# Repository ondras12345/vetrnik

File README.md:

# vetrnik
Power electronics for heating water using power generated by a small wind
turbine.

## Features / design goals
- No battery.
- Maximum power point tracking.
- Power to resistive heating elements is AC to prevent electrolytic corrosion.
- MQTT telemetry.
- Home Assistant integration via MQTT.
- Energy meter.
- Calculates RPM from wind turbine AC output frequency.
- Survives full 50 V / 40 A during normal operation, as well as significantly
  higher open-circuit voltage.

The device offers a feature-rich command line interface:
```
vetrnik-control:$ help
---- Available commands ----

SPIflash: Issue commands to SPI flash
conf: Get or set configuration options.
control: Get or set params of control algorithm.
debug: Filter debug messages
dfu: Switch to DFU firmware download mode.
ds18b20: Print out DS18B20 sensor readings
free: Print out amount of free memory.
ifconfig: Print out networking information.
lisp: Process a line of Lisp
lisp_read: Execute Lisp from file
lisp_reset: Reinit Lisp interpreter
log: Print log / postmort
millis: Returns the number of milliseconds passed since the program started.
mqtt: Print out MQTT status.
onewirescan: Scan devices on onewire bus
ota: Switch to over-the-air firmware dl mode.
power: Print status of power PCB or set params.
pump: Control circulation pump.
reset: Reset the MCU.
rx: Print out RX_datapoints.
rx_raw: Toggle printing of messages from power board.
stats: Get stats (energy, ...)
tx: Set value of TX datapoint.
tx_raw: Transmit message to power board.
uptime: Returns the time passed since the program started.
ver: Print out version info.
watch: Run command every second.

vetrnik-control:$ stats
stats:
energy: 0.000 kWh

vetrnik-control:$ power
power board status:
retrieved_millis: 2274816315
valid: 1
time: 56810 s
mode: 2
duty: 0 (0-255)
OCP_max_duty: 255 (0-255)
RPM: 0 RPM
voltage: 0.0 V
current: 0.000 A
enabled.hardware: 1
enabled.software: 1
enabled.overall: 1
emergency: 0
temperature_heatsink: 16.3 'C
temperature_rectifier: 16.4 'C
fan: 0
error_count: 0
last5m: 0

vetrnik-control:$ ds18b20
This command does NOT request a new conversion.
[0] voda: 28.93 C
[1] : 0.00 C
[2] : 0.00 C
[3] : 0.00 C
[4] : 0.00 C
[5] : 0.00 C
[6] : 0.00 C
[7] : 0.00 C
[8] : 0.00 C
[9] : 0.00 C

vetrnik-control:$ SPIflash -h
Usage: SPIflash [erase_chip|ls | create name length erasable | rm name
   | dump name start | dumpchip start | erase filename | ed filename start]

vetrnik-control:$ SPIflash ls
Files:
address (HEX)	name	size (Bytes)
010000	settings	65536
020000	init.lisp	65536

vetrnik-control:$ lisp (= test (/ (+ 1 3) 2))
nil
Success: 1

vetrnik-control:$ lisp test
2
Success: 1

vetrnik-control:$ log
Usage: log (all|new)

vetrnik-control:$ log all
Printing whole log...
---
[      0] event: 0x0D log reinit
[      0] boot: 0x05 POWER-ON_RESET (POR) / POWER-DOWN_RESET (PDR)
[      0] event: 0x00 Eth begin
[      5] event: 0x01 Eth got IP
[      5] control strategy: old=control_shorted new=control_shorted
[      5] MQTT state: -1 DISCONNECTED
[     20] event: 0x03 MQTT connected
[     21] MQTT state: 0 CONNECTED
[   6315] control strategy: old=control_shorted new=control_lisp
[  82610] event: 0x10 DS18B20 error
[ 966931] MQTT state: -3 CONNECTION_LOST
[ 966932] event: 0x03 MQTT connected
[ 966932] MQTT state: 0 CONNECTED
[3386627] MQTT state: -2 CONNECT_FAILED
[3386810] event: 0x03 MQTT connected
[3386810] MQTT state: 0 CONNECTED
[3386870] event: 0x03 MQTT connected
[3387652] MQTT state: -3 CONNECTION_LOST
[3387652] event: 0x03 MQTT connected
[3387652] MQTT state: 0 CONNECTED
[3387712] event: 0x03 MQTT connected
[3387772] MQTT state: -3 CONNECTION_LOST
[3387772] event: 0x03 MQTT connected
[3387772] MQTT state: 0 CONNECTED
[3387814] control strategy: old=control_lisp new=control_shorted
[      0] boot: 0x04 SOFTWARE_RESET
[      0] event: 0x00 Eth begin
[      5] event: 0x01 Eth got IP
[      5] control strategy: old=control_shorted new=control_shorted
[      5] MQTT state: -1 DISCONNECTED
[     20] event: 0x03 MQTT connected
[     20] MQTT state: 0 CONNECTED
[     28] MQTT receive: length=1
[     29] MQTT receive: length=11
[     29] control strategy: old=control_shorted new=control_lisp
[ 118759] MQTT state: -3 CONNECTION_LOST
[ 118760] event: 0x03 MQTT connected
[ 118760] MQTT state: 0 CONNECTED
[ 721373] MQTT state: -3 CONNECTION_LOST
[ 721373] MQTT state: -2 CONNECT_FAILED
[ 721414] event: 0x03 MQTT connected
[ 721414] MQTT state: 0 CONNECTED
[ 982793] MQTT state: -3 CONNECTION_LOST
[ 982794] event: 0x03 MQTT connected
[ 982794] MQTT state: 0 CONNECTED
[ 983379] MQTT state: -3 CONNECTION_LOST
[ 983380] event: 0x03 MQTT connected
[ 983380] MQTT state: 0 CONNECTED
[2274043] MQTT receive: length=1
[2274062] MQTT receive: length=1
done

vetrnik-control:$
```

## Hardware details
See [`hardware/`](hardware/).

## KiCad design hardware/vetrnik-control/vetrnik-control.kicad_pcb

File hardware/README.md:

# Vetrnik hardware
Block diagram:
```
            3 phase
+---------+ contactor +-----------+ DC +--------+ +-----------+ 1-phase +---------+
| Turbine +-+__/ __---+ rectifier +-+--+ ACS770 +-+ H-bridge  +---------+ heater  +
+---------+ |  ^      +-----------+ |  +----+---+ +-----------+ AC      +---------+
            |  |                    |       |          ^
            |  |             voltage|       |          |
            |  |                    |       | current  | duty
            |  |                    v       |          |
  frequency |  |      +-------------+-+     |          |
  (RPM)     |  +------+ vetrnik-power +<----+          |
            +-------->+               +----------------+
                      +-------+-------+
                              ^
                              | UART
                              v
                      +-------+-----------+
                      |  vetrnik-control  |
                      |                   +<----------> Ethernet
                      +-------------------+
```

The hardware consists of several PCBs in a custom-made enclosure. Most PCBs
are single-sided and designed to be milled out on a CNC.
- vetrnik-power
  - Controlled by an ATmega8 MCU.
  - Controls a FET H-bridge mounted on a heatsink.
  - Has isolated power supply, its GNDPWR is at wind turbine output potential.
  - Receives commands from vetrnik-control via optically isolated UART.
  - No remote firmware updates, no bootloader.
  - This PCB also contains analog comparator-based emergency stop circuitry
    that handles over-voltage condition even if the MCU is not working.
- vetrnik-control
  - Controlled by STM32F401.
  - Handles smart features (Ethernet, telnet, MQTT).
  - Implements LISP-like interpreted language that can be used to send
    commands to vetrnik-power. MPPT controller is implemented on this device
    in LISP.
  - Supports OTA firmware updates.
- vetrnik-current-sensor
  - A double-sided PCB with heavy copper. It passes all the current from the
    bridge rectifier through an ACS770-050U hall-effect current sensor.
- vetrnik-current-sensor-opamp
  - This PCB contains some additional signal-conditioning circuitry to improve
    current sensing precision and filter out noise.
- vetrnik-power-supply
  - A power supply board that converts 12 V from MeanWell power supply to
    various voltage levels needed by the device.
    The 3.3V voltage regulator is switch mode, 5V regulator is linear.
- vetrnik-relays
  - This is just a simple board with 3 relays that can be used to switch 230V
    devices like the coil of the contactor used to disconnect the wind turbine
    output, and a circulator pump.

## Wind turbine
- iSta breeze i-2000 Windsafe
- three phase
- 2 kW nominal power, 2.2 kW max
- 6 pole pairs --> 10 RPM / Hz

## Load
- 4x 600 W resistive heating element
- https://www.growzone.cz/48V-1200W-topna-patrona-G-6-4-palce-38x-197mm-d8275.htm

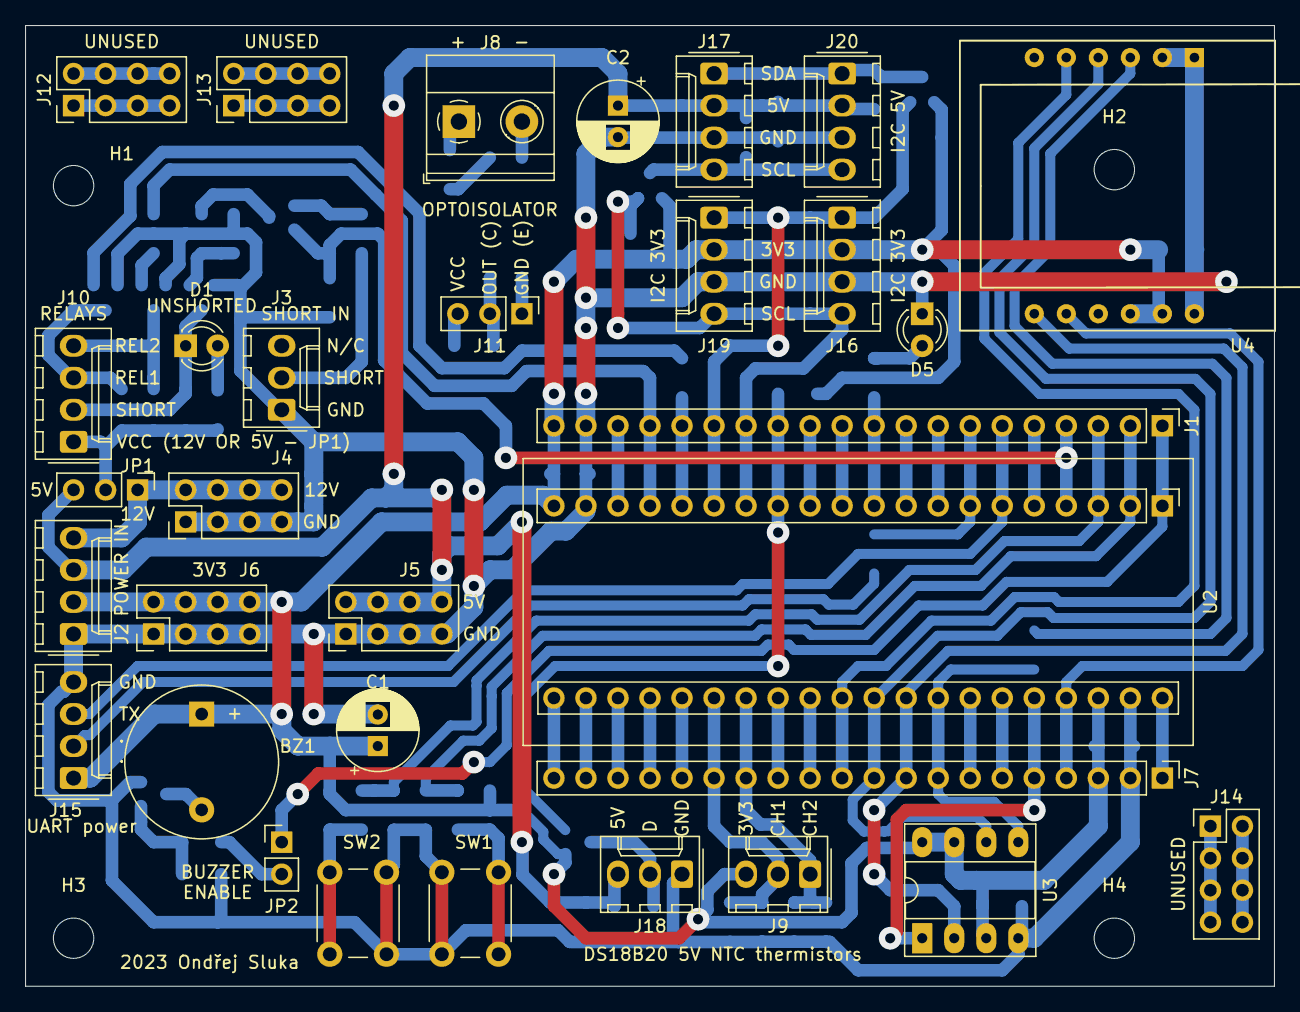
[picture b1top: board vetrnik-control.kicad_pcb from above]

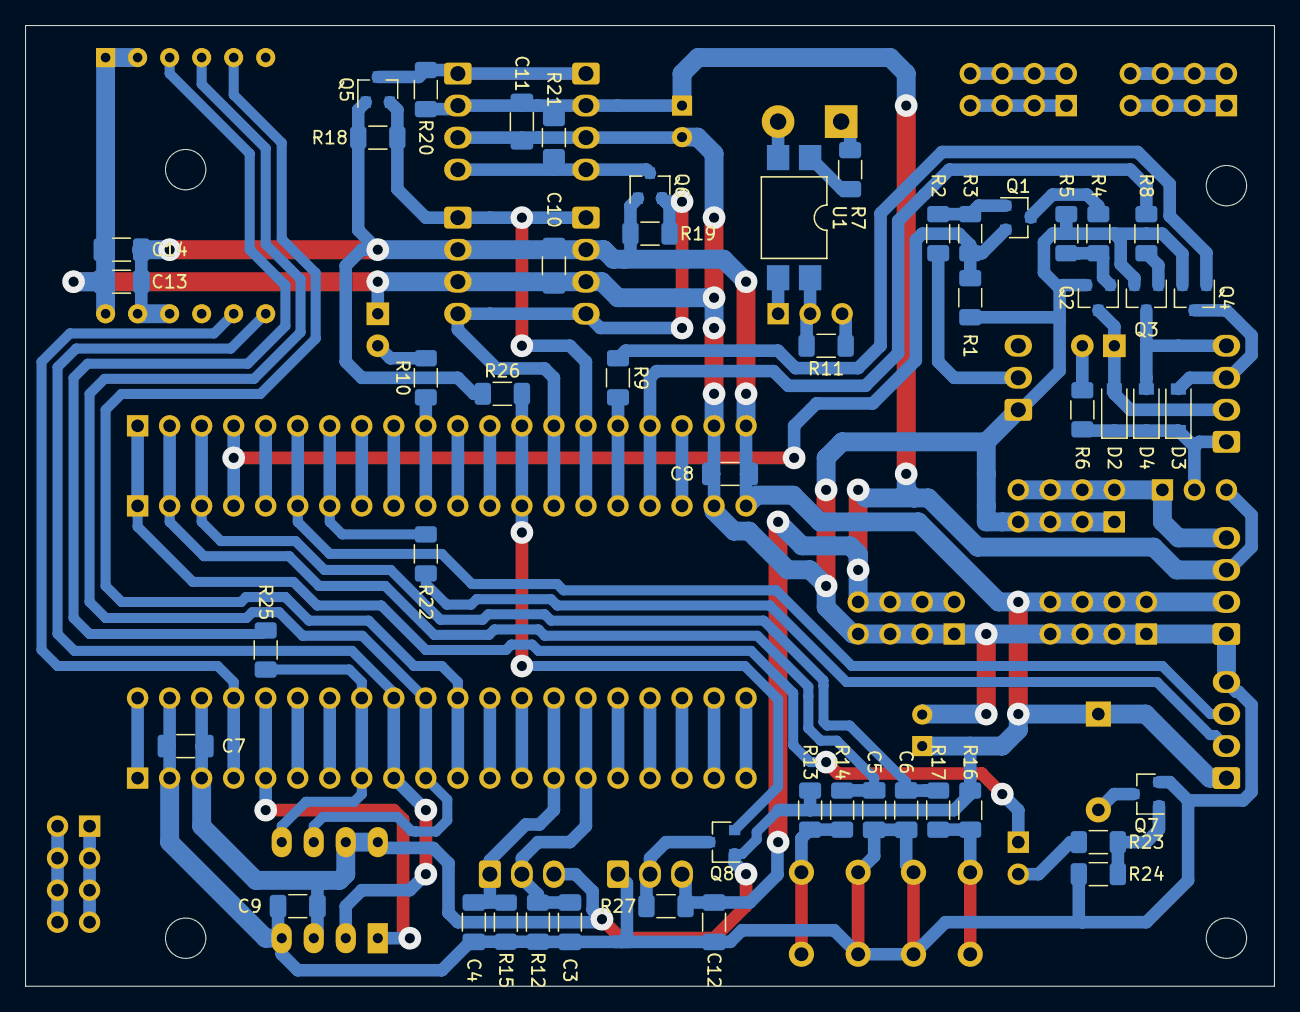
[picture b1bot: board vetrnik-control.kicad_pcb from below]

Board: 2 copper layers, 99.1 x 76.2 mm, 87 parts (51 on the bottom side), 74 nets.

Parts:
BZ1: Buzzer; Buzzer_12x9.5RM7.6
C1, C2: 100u; CP_Radial_D6.3mm_P2.50mm
C3, C4, C5, C6, C7, C9, C10, C11, C12, C13: 100n; C_1206_3216Metric_Pad1.33x1.80mm_HandSolder
C8, C14: 10u; C_1206_3216Metric_Pad1.33x1.80mm_HandSolder
D1: GREEN; LED_D3.0mm
D2, D3, D4: 1N4148W; D_SOD-123
D5: RED; LED_D3.0mm
H1, H2, H3, H4: MountingHole; MountingHole_3.2mm_M3
J1, J7: Conn_01x20_Male; PinHeader_1x20_P2.54mm_Vertical
J2, J10, J15, J16, J17, J19, J20: Conn_01x04; Molex_KK-254_AE-6410-04A_1x04_P2.54mm_Vertical
J3, J9, J18: Conn_01x03; Molex_KK-254_AE-6410-03A_1x03_P2.54mm_Vertical
J4, J5, J6, J12, J13, J14: Conn_02x04_Odd_Even; PinHeader_2x04_P2.54mm_Vertical
J8: Screw_Terminal_01x02; TerminalBlock_Phoenix_MKDS-1,5-2_1x02_P5.00mm_Horizontal
J11: Conn_01x03_Male; PinHeader_1x03_P2.54mm_Vertical
JP1: Jumper_3_Bridged12; PinHeader_1x03_P2.54mm_Vertical
JP2: Jumper; PinHeader_1x02_P2.54mm_Vertical
Q1: BC857; SOT-23
Q2, Q3, Q4, Q7: BC847; SOT-23
Q5, Q6, Q8: BSS138; SOT-23
R1, R3, R5, R11, R13, R14, R16, R17, R18, R19, R20, R21, R24, R26, R27: 10k; R_1206_3216Metric_Pad1.30x1.75mm_HandSolder
R2, R4, R6, R7, R8, R9, R23: 1k; R_1206_3216Metric_Pad1.30x1.75mm_HandSolder
R10: 330; R_1206_3216Metric_Pad1.30x1.75mm_HandSolder
R12, R15: 4k7; R_1206_3216Metric_Pad1.30x1.75mm_HandSolder
R22, R25: 0; R_1206_3216Metric_Pad1.30x1.75mm_HandSolder
SW1, SW2: SW_Push; SW_PUSH_6mm_H4.3mm
U1: LTV-817S; SMDIP-4_W9.53mm
U2: YAAJ_WeAct_BlackPill_Part_Like; YAAJ_WeAct_BlackPill_2
U3: MX25L8006EM1I-12G; DIP-8_W7.62mm_Socket_LongPads
U4: WIZ850io

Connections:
+3V3: BZ1.1, C1.1, C7.1, C8.1, C9.1, C10.1, C13.1, C14.1, J1.20, J2.2, J6.2, J6.4, J6.6, J6.8, J7.3, J9.3, J15.1, J16.2, J19.2, Q5.1, Q6.1, Q8.1, R13.1, R16.1, R18.1, R19.1, R26.1, U2.20, U2.38, U3.3, U3.7, U3.8, U4.10, U4.11
+5V: C2.1, C11.1, C12.1, J2.3, J5.2, J5.4, J5.6, J5.8, J17.2, J18.3, J20.2, JP1.3, R20.1, R21.1, R27.1
+12V: J2.4, J4.2, J4.4, J4.6, J4.8, JP1.1
/ADC_NTC1: C3.1, J7.15, J9.2, R12.1, U2.26
/ADC_NTC2: C4.1, J7.14, J9.1, R15.1, U2.27
/BUTTON1: C5.1, J1.2, R14.1, U2.2
/BUTTON2: C6.1, J1.3, R17.1, U2.3
/BUZZER: J1.1, JP2.1, U2.1
/MCU_18: J1.18, U2.18
/MCU_40: J7.1, U2.40
/MISO: J7.9, U2.32, U3.2, U4.7
/MOSI: J7.8, R25.2, U2.33, U3.5
/PA2: J7.13, U2.28
/PA3: J7.12, U2.29
/PA4: J7.11, U2.30, U4.5
/PA5: J7.10, U2.31, U3.6, U4.4
/PA8: J1.5, U2.5
/PA9: J1.6, J15.3, U2.6
/PA10: J1.7, R22.2, U2.7
/PA11: J1.8, U2.8
/PA12: J1.9, U2.9
/PA15: J1.10, R10.1, U2.10
/PB0: J7.7, U2.34
/PB1: J7.6, U2.35
/PB2: J7.5, U2.36, U3.1
/PB3: J1.11, U2.11
/PB4: J1.12, U2.12
/PB5: J1.13, Q8.2, R26.2, U2.13
/PB6: J1.14, J16.4, J19.4, Q6.2, R19.2, U2.14
/PB7: J1.15, J16.1, J19.1, Q5.2, R18.2, U2.15
/PB8: J1.16, R9.2, U2.16
/PB9: J1.17, R8.2, U2.17
/PB10: J7.4, U2.37, U4.8
/PB15: J1.4, Q1.2, R1.1, R3.1, U2.4
/PC13: J7.19, U2.22
/PC14: J7.18, U2.23
/PC15: J7.17, U2.24
/RES: J7.16, U2.25
/SCL_5V: J17.4, J20.4, Q6.3, R21.2
/SDA_5V: J17.1, J20.1, Q5.3, R20.2
/VBat: J7.20, U2.21
/onewire_5V: J18.2, Q8.3, R27.2
GND: C1.2, C2.2, C3.2, C4.2, C5.2, C6.2, C7.2, C8.2, C9.2, C10.2, C11.2, C12.2, C13.2, C14.2, D5.1, J1.19, J2.1, J3.1, J4.1, J4.3, J4.5, J4.7, J5.1, J5.3, J5.5, J5.7, J6.1, J6.3, J6.5, J6.7, J7.2, J15.4, J16.3, J17.3, J18.1, J19.3, J20.3, Q2.2, Q3.2, Q4.2, Q7.2, R1.2, R5.2, R12.2, R15.2, R24.2, SW1.2, SW2.2, U2.19, U2.39, U3.4, U4.1, U4.2, U4.12
unnamed: BZ1.2, Q7.3
unnamed: D1.1, D2.2, J10.2, Q2.3
unnamed: D1.2, R6.2
unnamed: D2.1, D3.1, D4.1, J10.1, JP1.2, R6.1
unnamed: D3.2, J10.3, Q4.3
unnamed: D4.2, J10.4, Q3.3
unnamed: D5.2, R10.2
unnamed: J3.2, R2.2
unnamed: J8.1, R7.2
unnamed: J8.2, U1.2
unnamed: J11.1, U1.3
unnamed: J11.2, R11.2, U1.4
unnamed: J11.3, R11.1
unnamed: J12.1, J12.3, J12.5, J12.7
unnamed: J12.2, J12.4, J12.6, J12.8
unnamed: J13.1, J13.3, J13.5, J13.7
unnamed: J13.2, J13.4, J13.6, J13.8
unnamed: J14.1, J14.3, J14.5, J14.7
unnamed: J14.2, J14.4, J14.6, J14.8
unnamed: J15.2, R22.1
unnamed: JP2.2, R23.2
unnamed: Q1.1, R2.1, R3.2
unnamed: Q1.3, R4.2
unnamed: Q2.1, R4.1, R5.1
unnamed: Q3.1, R8.1
unnamed: Q4.1, R9.1
unnamed: Q7.1, R23.1, R24.1
unnamed: R7.1, U1.1
unnamed: R13.2, R14.2, SW1.1
unnamed: R16.2, R17.2, SW2.1
unnamed: R25.1, U4.3

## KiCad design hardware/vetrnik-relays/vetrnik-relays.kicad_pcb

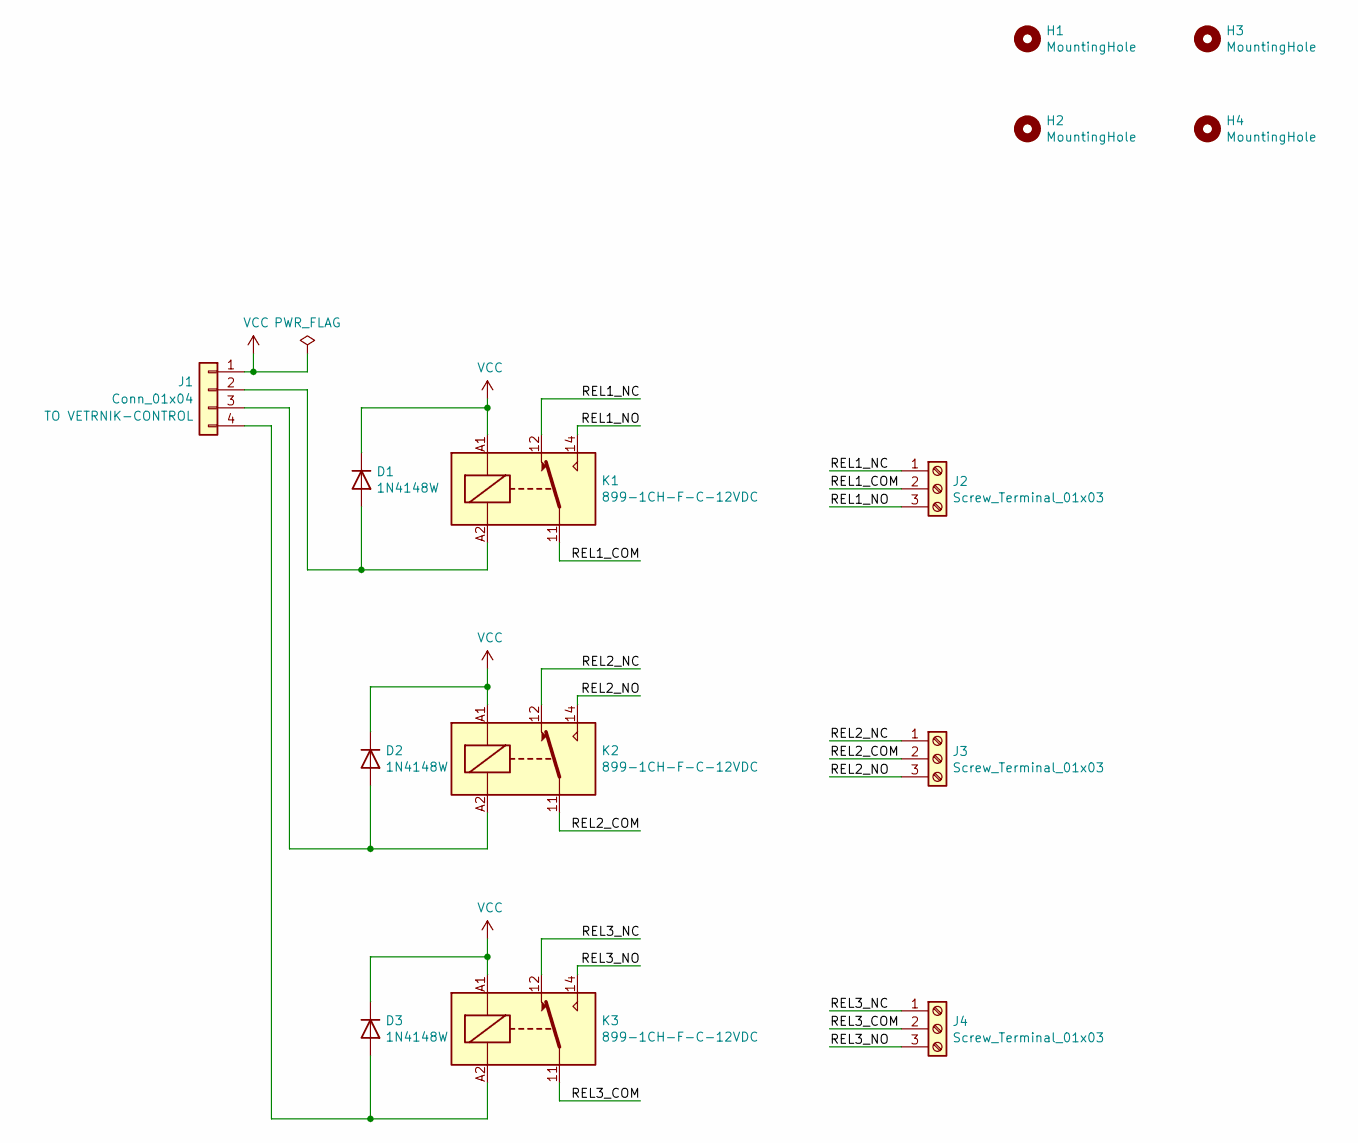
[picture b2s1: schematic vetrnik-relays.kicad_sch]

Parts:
D1, D2, D3: 1N4148W; D_SOD-123
H1, H2, H3, H4: MountingHole; MountingHole_3.2mm_M3
J1: Conn_01x04; Molex_KK-254_AE-6410-04A_1x04_P2.54mm_Vertical
J2, J3, J4: Screw_Terminal_01x03; TerminalBlock_Phoenix_MKDS-1,5-3_1x03_P5.00mm_Horizontal
K1, K2, K3: 899-1CH-F-C-12VDC; Relay_SPDT_Finder_36.11

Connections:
/REL1_COM: J2.2, K1.11
/REL1_NC: J2.1, K1.12
/REL1_NO: J2.3, K1.14
/REL2_COM: J3.2, K2.11
/REL2_NC: J3.1, K2.12
/REL2_NO: J3.3, K2.14
/REL3_COM: J4.2, K3.11
/REL3_NC: J4.1, K3.12
/REL3_NO: J4.3, K3.14
unnamed: D1.2 (A), J1.2, K1.A2
unnamed: D2.2 (A), J1.3, K2.A2
unnamed: D3.2 (A), J1.4, K3.A2
VCC: D1.1 (K), D2.1 (K), D3.1 (K), J1.1, K1.A1, K2.A1, K3.A1

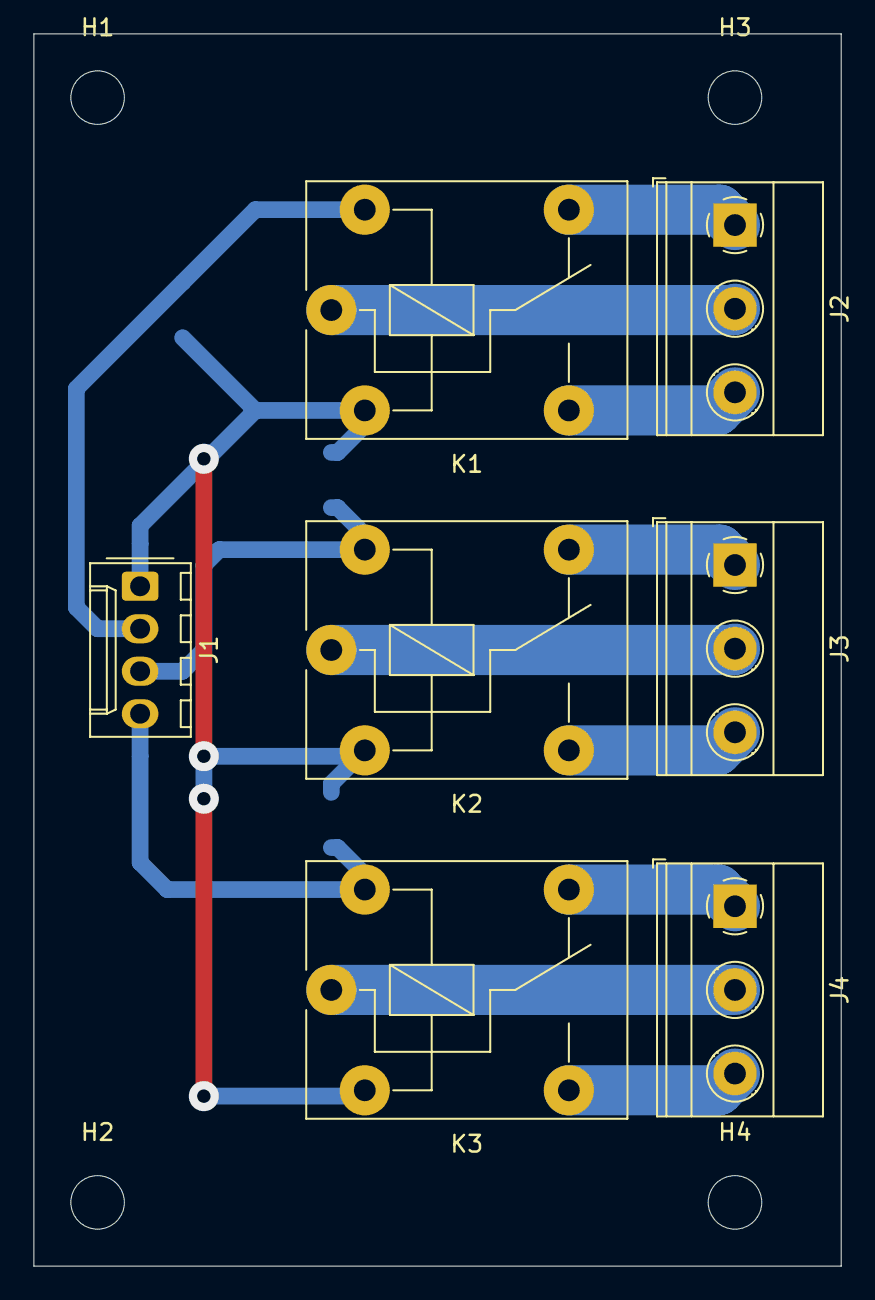
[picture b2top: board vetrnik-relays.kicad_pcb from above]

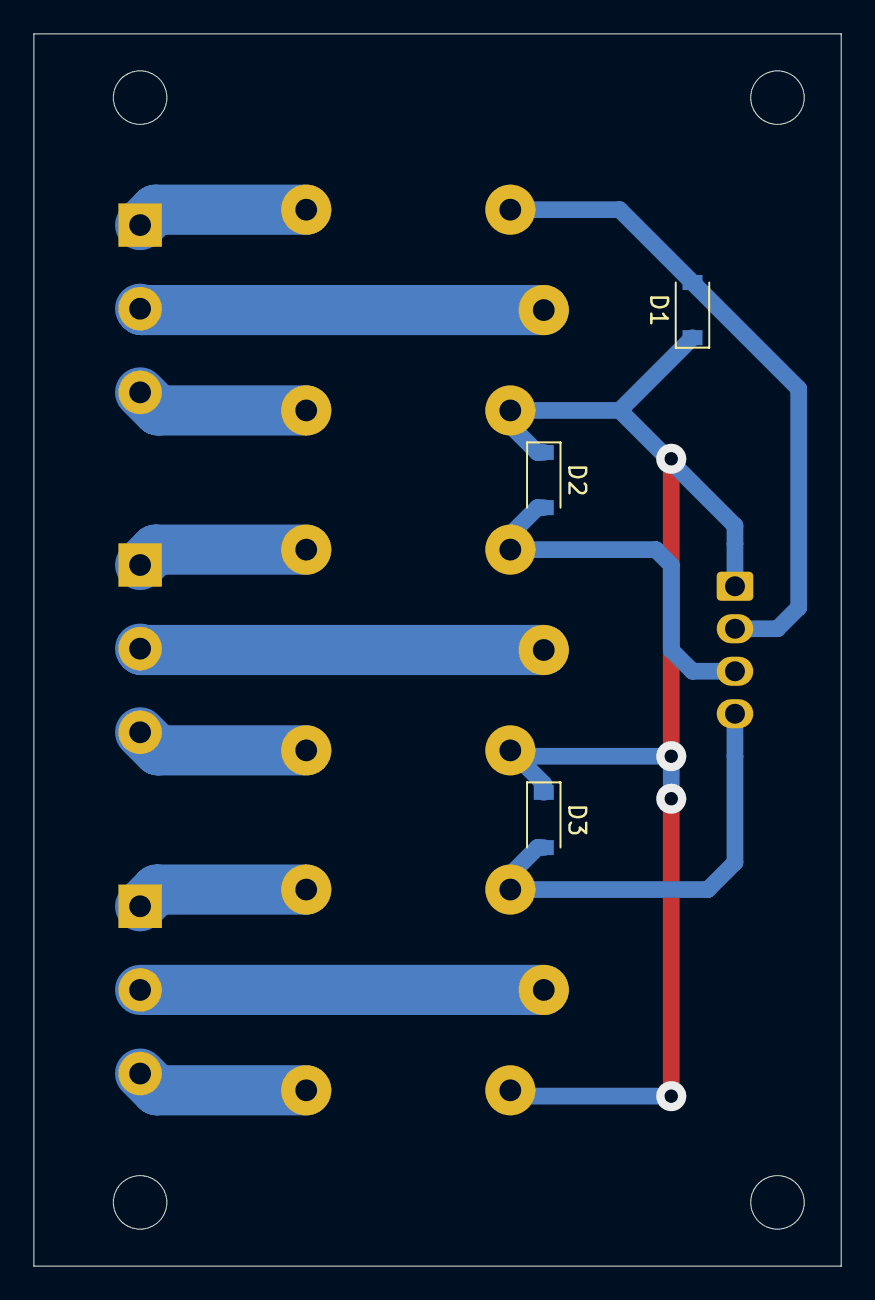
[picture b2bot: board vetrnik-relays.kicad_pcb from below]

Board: 2 copper layers, 48.3 x 73.7 mm, 14 parts (3 on the bottom side), 13 nets.

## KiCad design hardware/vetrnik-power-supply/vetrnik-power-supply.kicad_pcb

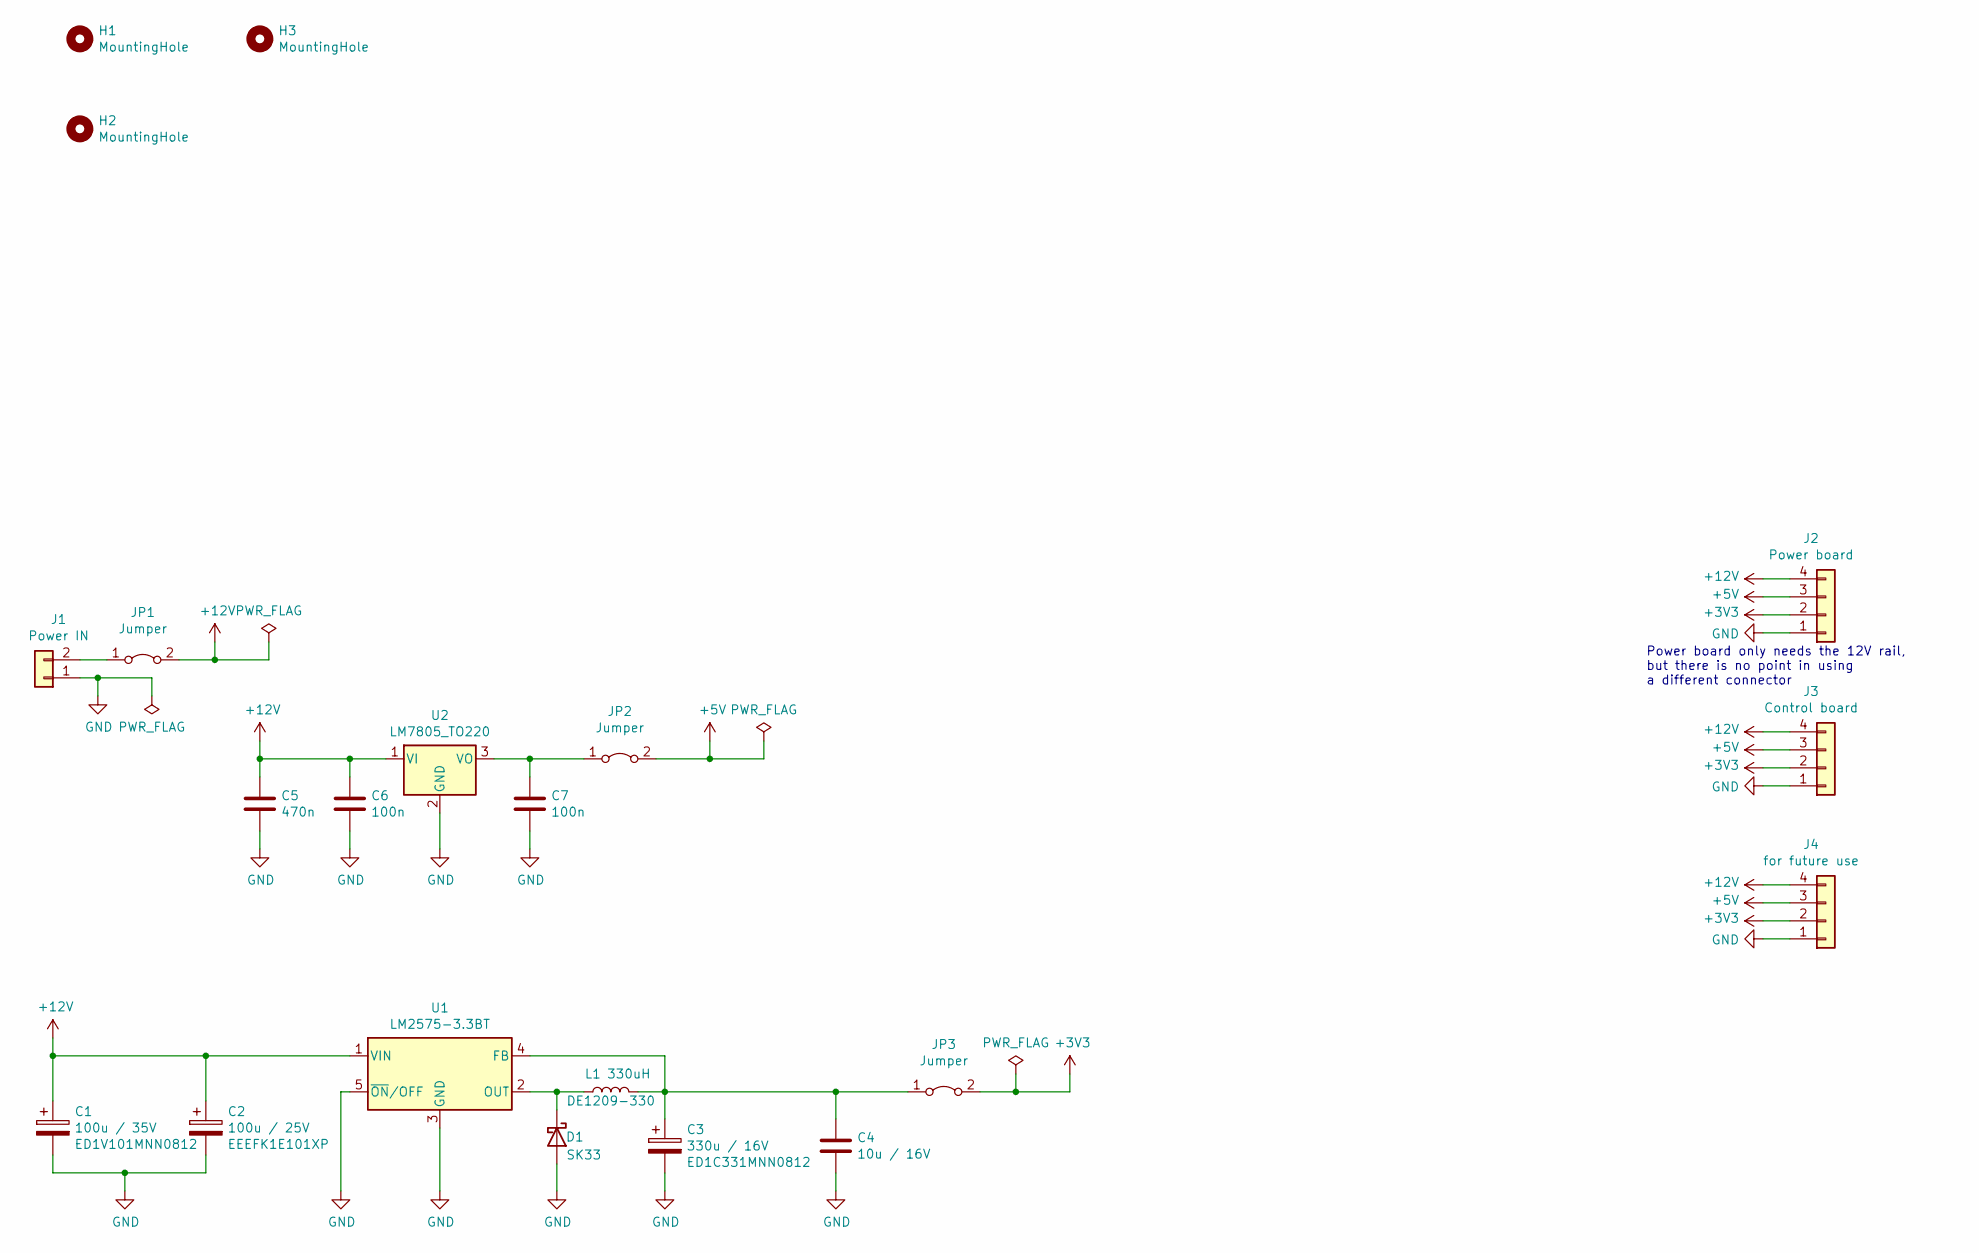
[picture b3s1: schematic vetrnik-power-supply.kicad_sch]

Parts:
C1: 100u / 35V; CP_Radial_D8.0mm_P3.50mm; Part Number ED1V101MNN0812
C2: 100u / 25V; CP_Elec_6.3x7.7; Part Number EEEFK1E101XP
C3: 330u / 16V; CP_Radial_D8.0mm_P3.50mm; Part Number ED1C331MNN0812
C4: 10u / 16V; C_1206_3216Metric_Pad1.33x1.80mm_HandSolder
C5: 470n; C_1206_3216Metric_Pad1.33x1.80mm_HandSolder
C6, C7: 100n; C_1206_3216Metric_Pad1.33x1.80mm_HandSolder
D1: SK33; D_SMC_Handsoldering
H1, H2, H3: MountingHole; MountingHole_3.2mm_M3
J1: Conn_01x02; Molex_KK-254_AE-6410-02A_1x02_P2.54mm_Vertical
J2, J3, J4: Conn_01x04; Molex_KK-254_AE-6410-04A_1x04_P2.54mm_Vertical
JP1, JP2, JP3: Jumper; PinHeader_1x02_P2.54mm_Vertical
L1: 330uH; L_12x12mm_H8mm; Part Number DE1209-330
U1: LM2575-3.3BT; TO-220-5_Vertical
U2: LM7805_TO220; TO-220-3_Vertical

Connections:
+3V3: J2.2, J3.2, J4.2, JP3.2 (B)
+5V: J2.3, J3.3, J4.3, JP2.2 (B)
+12V: C1.1, C2.1, C5.1, C6.1, J2.4, J3.4, J4.4, JP1.2 (B), U1.1 (VIN), U2.1 (VI)
GND: C1.2, C2.2, C3.2, C4.2, C5.2, C6.2, C7.2, D1.2 (A), J1.1, J2.1, J3.1, J4.1, U1.3 (GND), U1.5 (~ON/OFF), U2.2 (GND)
unnamed: D1.1 (K), L1.1, U1.2 (OUT)
unnamed: J1.2, JP1.1 (A)
unnamed: C7.1, JP2.1 (A), U2.3 (VO)
unnamed: C3.1, C4.1, JP3.1 (A), L1.2, U1.4 (FB)

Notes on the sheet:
Power board only needs the 12V rail, but there is no point in using a different connector

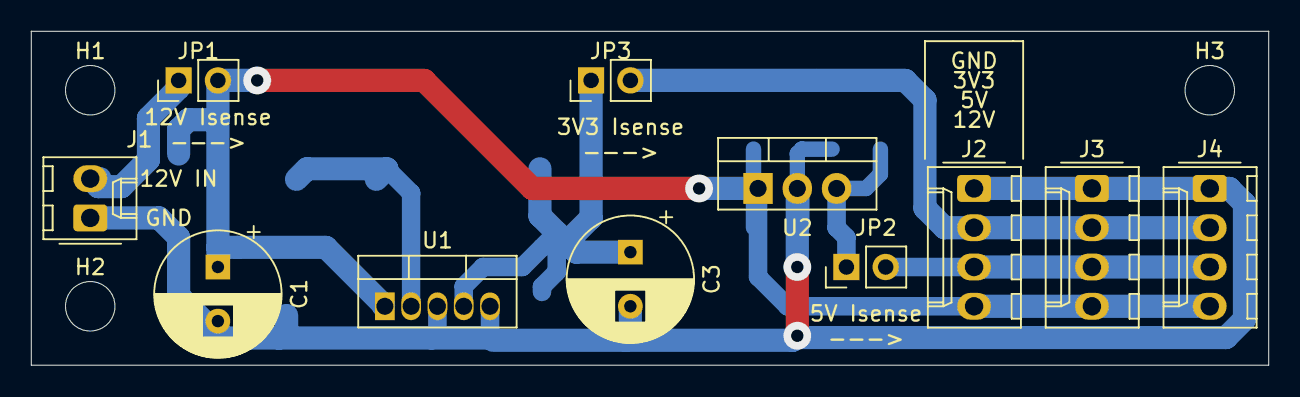
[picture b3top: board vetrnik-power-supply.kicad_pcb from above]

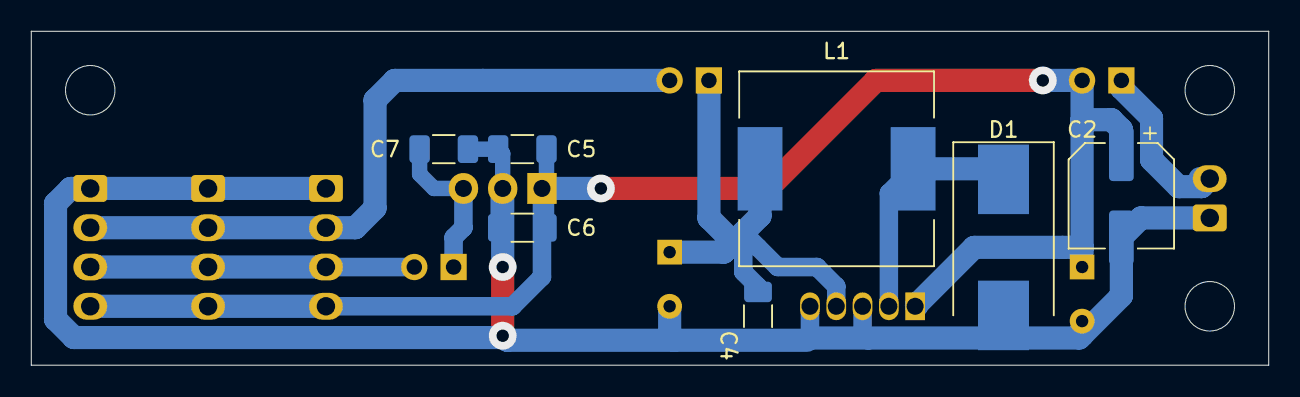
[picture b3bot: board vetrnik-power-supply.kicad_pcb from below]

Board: 2 copper layers, 80.0 x 21.6 mm, 21 parts (7 on the bottom side), 8 nets.

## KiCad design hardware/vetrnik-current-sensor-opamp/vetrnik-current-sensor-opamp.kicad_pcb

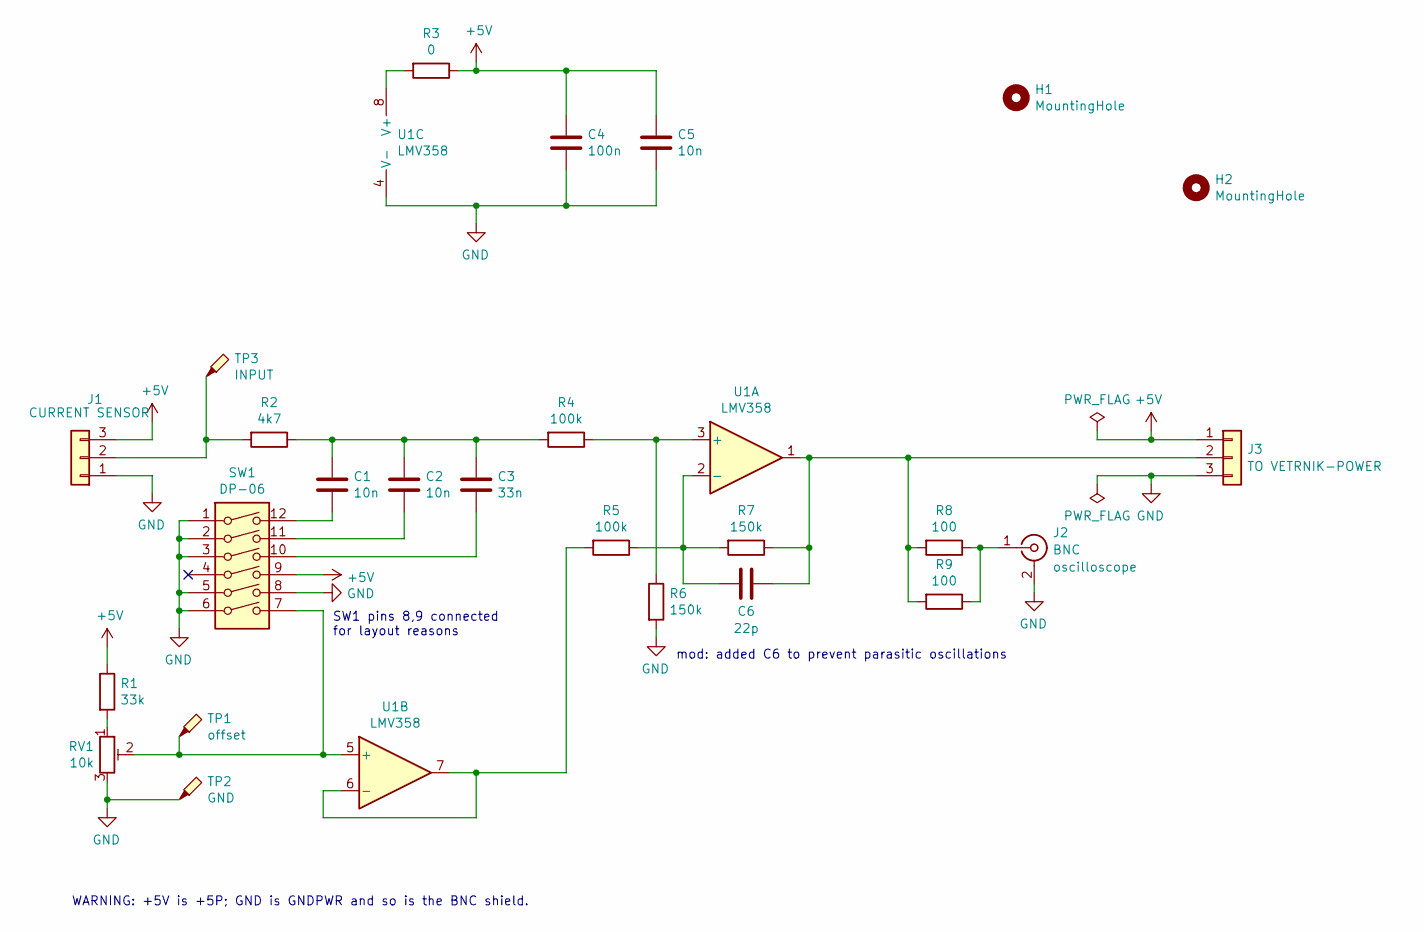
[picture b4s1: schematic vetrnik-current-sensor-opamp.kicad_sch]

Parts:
C1, C2, C5: 10n; C_1206_3216Metric_Pad1.33x1.80mm_HandSolder
C3: 33n; C_1206_3216Metric_Pad1.33x1.80mm_HandSolder
C4: 100n; C_1206_3216Metric_Pad1.33x1.80mm_HandSolder
C6: 22p
H1, H2: MountingHole; MountingHole_3.2mm_M3
J1, J3: Conn_01x03; Molex_KK-254_AE-6410-03A_1x03_P2.54mm_Vertical
J2: BNC; BNC_PanelMountable_Vertical
R1: 33k; R_1206_3216Metric_Pad1.30x1.75mm_HandSolder
R2: 4k7; R_1206_3216Metric_Pad1.30x1.75mm_HandSolder
R3: 0; R_1206_3216Metric_Pad1.30x1.75mm_HandSolder
R4, R5: 100k; R_1206_3216Metric_Pad1.30x1.75mm_HandSolder
R6, R7: 150k; R_1206_3216Metric_Pad1.30x1.75mm_HandSolder
R8, R9: 100; R_1206_3216Metric_Pad1.30x1.75mm_HandSolder
RV1: 10k; Potentiometer_Bourns_3296W_Vertical
SW1: DP-06; SW_DIP_SPSTx06_Piano_10.8x16.8mm_W7.62mm_P2.54mm
TP1: offset; PinSocket_1x01_P2.54mm_Vertical
TP2: GND; PinSocket_1x01_P2.54mm_Vertical
TP3: INPUT; PinSocket_1x01_P2.54mm_Vertical
U1: LMV358; SOIC-8_3.9x4.9mm_P1.27mm

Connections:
+5V: C4.1, C5.1, J1.3, J3.1, R1.1, R3.1, SW1.9
GND: C4.2, C5.2, J1.1, J2.2 (Ext), J3.3, R6.2, RV1.3, SW1.1, SW1.2, SW1.3, SW1.5, SW1.6, SW1.8, TP2.1, U1.4 (V-)
unnamed: C1.1, C2.1, C3.1, R2.1, R4.2
unnamed: C1.2, SW1.12
unnamed: C2.2, SW1.11
unnamed: C3.2, SW1.10
unnamed: J1.2, R2.2, TP3.1
unnamed: J2.1 (In), R8.1, R9.1
unnamed: C6.2, J3.2, R7.1, R8.2, R9.2, U1.1
unnamed: R1.2, RV1.1
unnamed: R3.2, U1.8 (V+)
unnamed: R4.1, R6.1, U1.3 (+)
unnamed: C6.1, R5.1, R7.2, U1.2 (-)
unnamed: R5.2, U1.6 (-), U1.7
unnamed: RV1.2, SW1.7, TP1.1, U1.5 (+)

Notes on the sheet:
WARNING: +5V is +5P; GND is GNDPWR and so is the BNC shield.
SW1 pins 8,9 connected for layout reasons
mod: added C6 to prevent parasitic oscillations

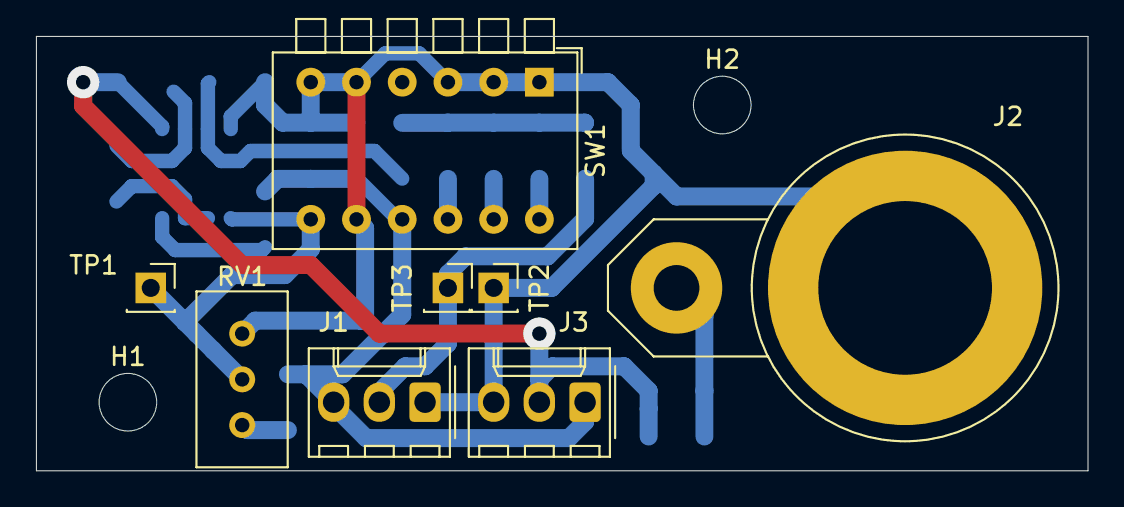
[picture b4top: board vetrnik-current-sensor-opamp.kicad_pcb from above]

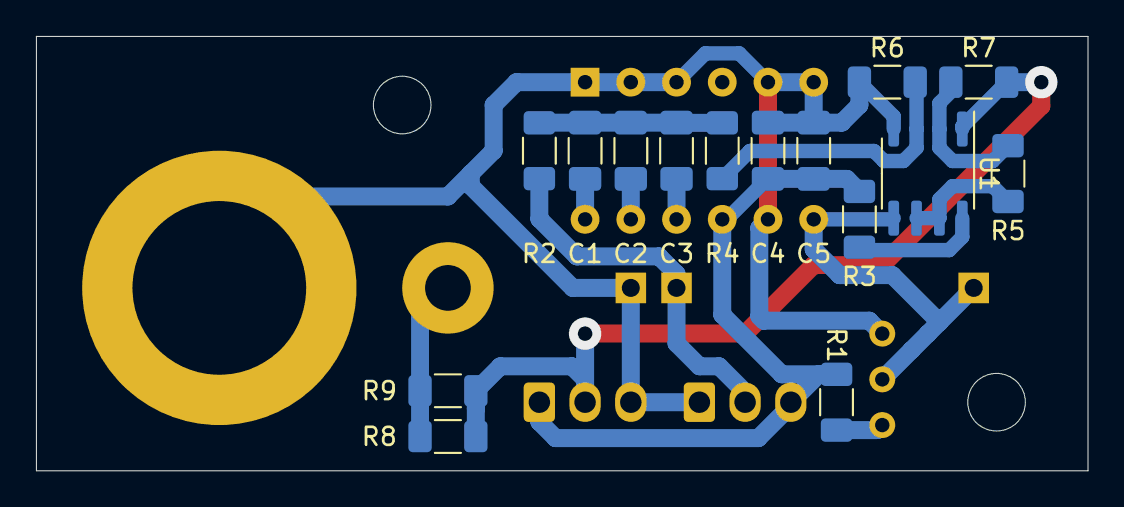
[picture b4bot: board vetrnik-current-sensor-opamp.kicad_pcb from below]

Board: 2 copper layers, 58.4 x 24.1 mm, 25 parts (15 on the bottom side), 15 nets.
